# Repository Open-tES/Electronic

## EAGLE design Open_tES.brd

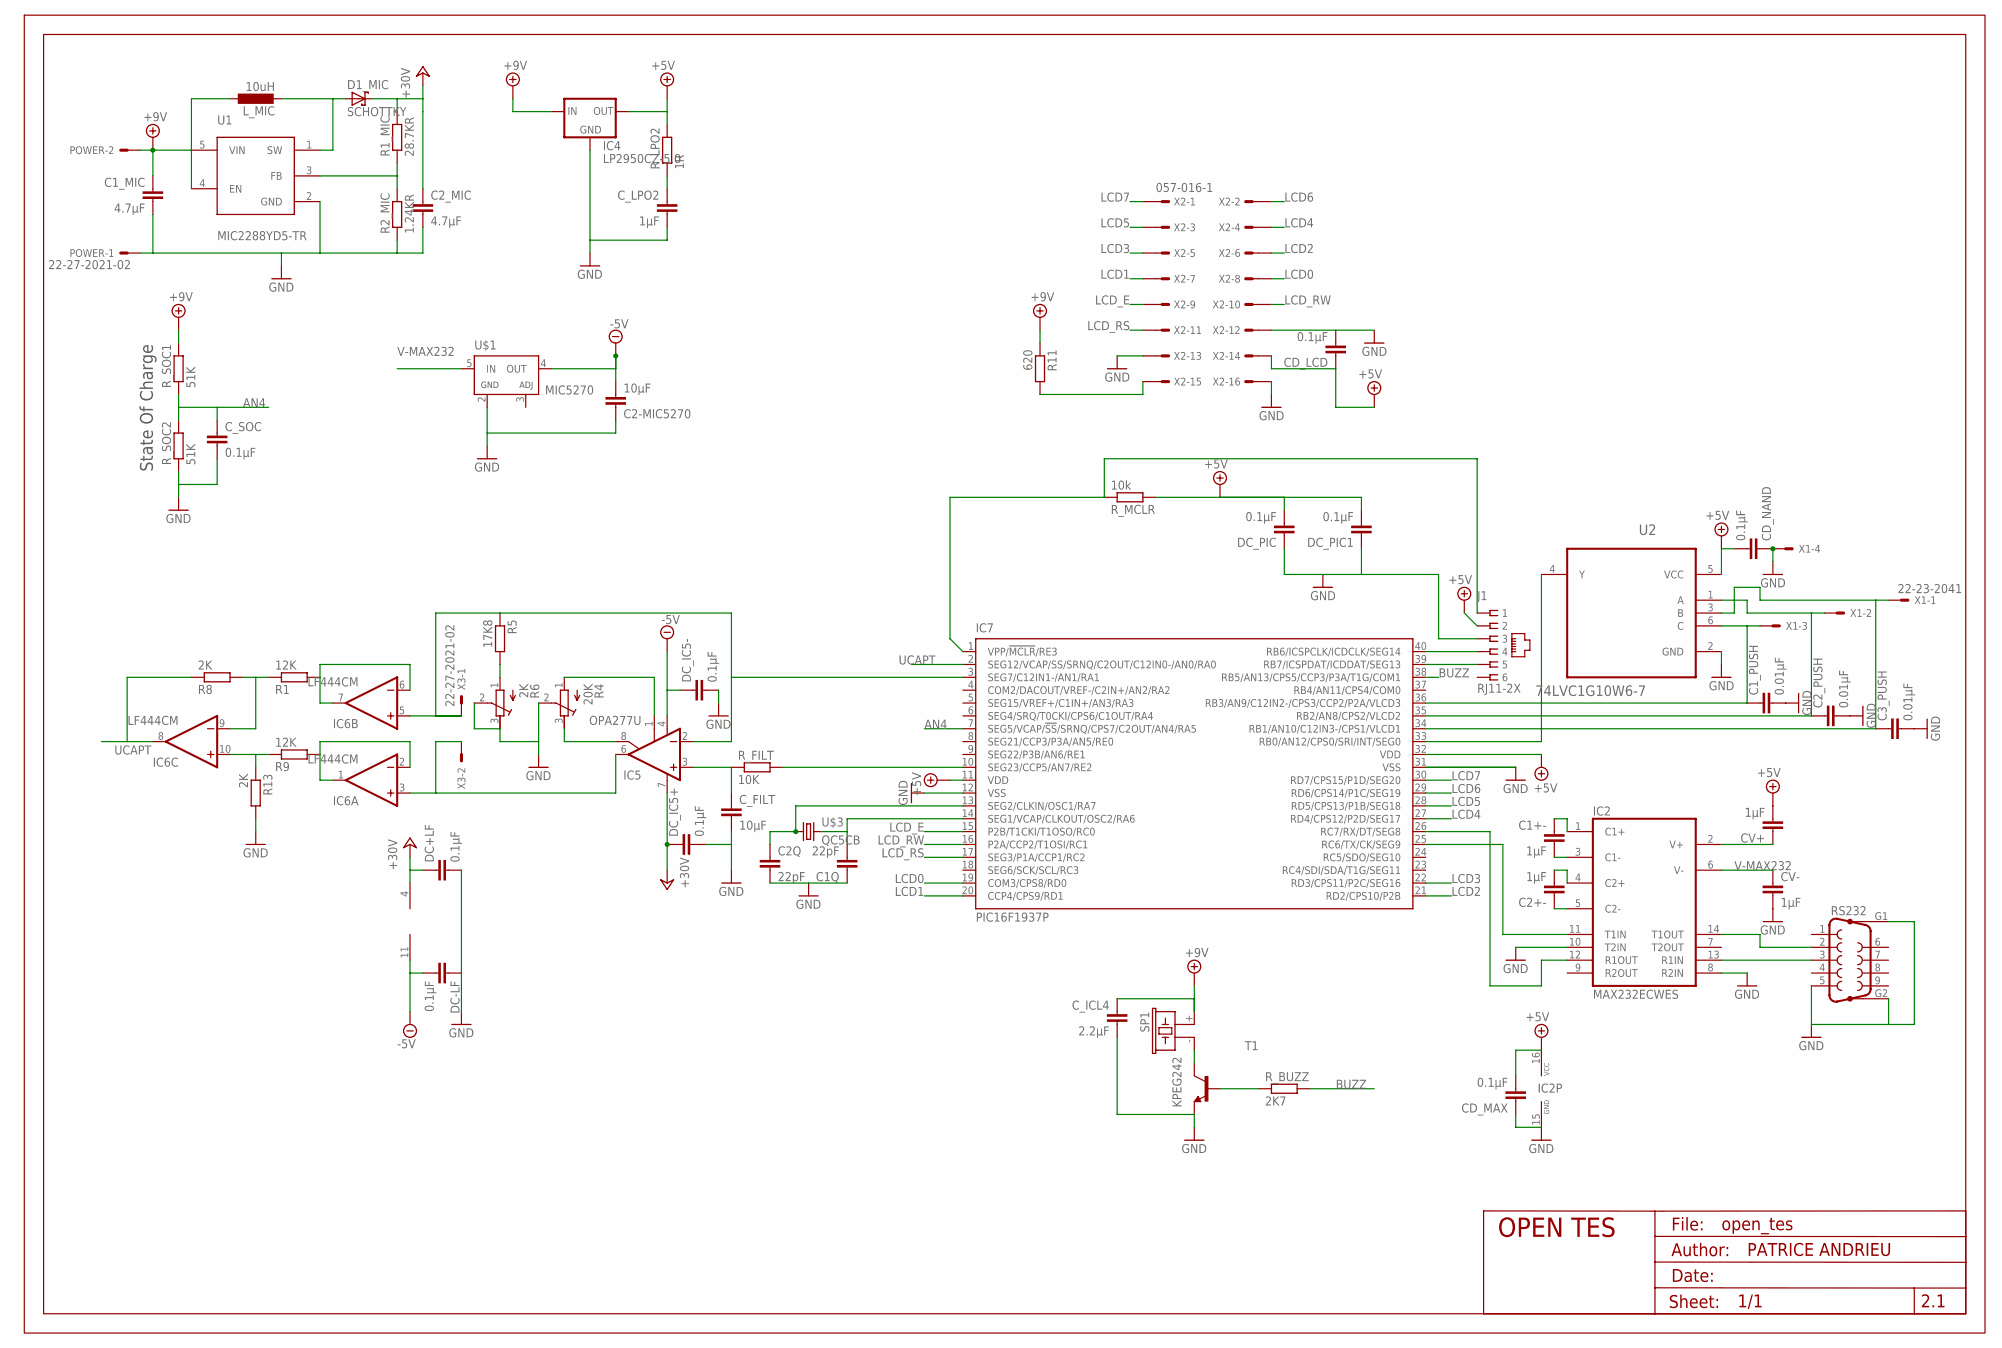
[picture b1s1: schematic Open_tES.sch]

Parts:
C1+-, C2+-: 1µF; C0805
C1Q, C2Q: 22pF; C0805
C1_MIC, C2_MIC: 4.7µF; C0805
C1_PUSH, C2_PUSH, C3_PUSH: 0.01µF; C0805
C2-MIC5270: 10µF; C0805
CD_LCD: 0.1µF; C0805
CD_MAX: 0.1µF; C0805
CD_NAND: 0.1µF; C0805
CV+: 1µF; C0805
CV-: 1µF; C0805
C_FILT: 10µF; C0805
C_ICL4: 2.2µF; C0805K
C_LPO2: 1µF; C0805
C_SOC: 0.1µF; C0805
D1_MIC: SCHOTTKY; SOD80
DC+LF: 0.1µF; C0805
DC-LF: 0.1µF; C0805
DC_IC5+, DC_IC5-: 0.1µF; C0805
DC_PIC, DC_PIC1: 0.1µF; C0805
IC2: MAX232ECWES; SO16
IC4: LP2950CZ-5.0; TO92
IC5: OPA277U; SO08
IC6: LF444CM; SO14
IC7: PIC16F1937P; DIL40
J1: RJ11-2X; RJ11-NO_SHIELD
L_MIC: 10uH; L2012C
POWER: 22-27-2021-02; 6410-02
R1, R9: 12K; R0805
R1_MIC: 28.7KR; R0805
R2_MIC: 1.24KR; R0805
R4: 20K; RTRIM3214W
R5: 17K8; M0805
R6: 2K; RTRIM3214W
R8, R13: 2K; R0805
R11: 620; 0204/7
RS232: F09HP
R_BUZZ: 2K7; R0805
R_FILT: 10K; R0805
R_LPO2: 1R; R0805
R_MCLR: 10k; 0204/7
R_SOC1, R_SOC2: 51K; R0805
SP1: KPEG242
T1: BFR92-NPN-SOT23-BEC; SOT23-BEC
U1: MIC2288YD5-TR; SOT23-5L
U2: 74LVC1G10W6-7; SOT95P280X135-6N
U$1: MIC5270; SOT23-5L
U$3: QC5CB
U$4: FRAME; OPEN_TE_VERSION
X1: 22-23-2041
X2: 057-016-1
X3: 22-27-2021-02; 6410-02

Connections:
+5V/1: CD_LCD.1, CD_MAX.2, CD_NAND.2, CV+.2, DC_PIC.2, DC_PIC1.2, IC2.16 (VCC), IC4.1 (OUT), IC7.11 (VDD), IC7.32 (VDD), J1.2, R_LPO2.2, R_MCLR.2, U2.5 (VCC), X2.14
+9V: C1_MIC.1, C_ICL4.1, IC4.3 (IN), L_MIC.1, POWER.2, R11.1, R_SOC1.2, SP1.+ (1), U1.4 (EN), U1.5 (VIN)
+30V: C2_MIC.1, D1_MIC.C, DC+LF.1, DC_IC5+.1, IC5.7 (V+), IC6.4 (V+), R1_MIC.2
-5V: C2-MIC5270.2, DC-LF.2, DC_IC5-.1, IC5.4 (V-), IC6.11 (V-), U$1.4 (OUT)
AN4: C_SOC.1, IC7.7 (SEG5/VCAP/!SS!/SRNQ/CPS7/C2OUT/AN4/RA5), R_SOC1.1, R_SOC2.2
BUZZ: IC7.38 (RB5/AN13/CPS5/CCP3/P3A/T1G/COM1), R_BUZZ.2
GND: C1Q.1, C1_MIC.2, C1_PUSH.2, C2-MIC5270.1, C2Q.2, C2_MIC.2, C2_PUSH.2, C3_PUSH.2, CD_LCD.2, CD_MAX.1, CD_NAND.1, CV-.2, C_FILT.2, C_ICL4.2, C_LPO2.2, C_SOC.2, DC+LF.2, DC-LF.1, DC_IC5+.2, DC_IC5-.2, DC_PIC.1, DC_PIC1.1, IC2.8 (R2IN), IC2.10 (T2IN), IC2.15 (GND), IC4.2 (GND), IC7.12 (VSS), IC7.31 (VSS), J1.3, POWER.1, R2_MIC.1, R4.2 (S), R6.2 (S), R6.3 (E), R13.2, RS232.5, RS232.G1, RS232.G2, R_SOC2.1, T1.E, U1.2 (GND), U2.2 (GND), U$1.2 (GND), X1.4, X2.12, X2.13, X2.16
ICAPT: IC5.2 (-IN), IC6.5 (+IN), IC7.3 (SEG7/C12IN1-/AN1/RA1), R5.1, X3.1
LCD0: IC7.19 (COM3/CPS8/RD0), X2.8
LCD1: IC7.20 (CCP4/CPS9/RD1), X2.7
LCD2: IC7.21 (RD2/CPS10/P2B), X2.6
LCD3: IC7.22 (RD3/CPS11/P2C/SEG16), X2.5
LCD4: IC7.27 (RD4/CPS12/P2D/SEG17), X2.4
LCD5: IC7.28 (RD5/CPS13/P1B/SEG18), X2.3
LCD6: IC7.29 (RD6/CPS14/P1C/SEG19), X2.2
LCD7: IC7.30 (RD7/CPS15/P1D/SEG20), X2.1
LCD_E: IC7.15 (P2B/T1CKI/T1OSO/RC0), X2.9
LCD_RS: IC7.17 (SEG3/P1A/CCP1/RC2), X2.11
LCD_RW: IC7.16 (P2A/CCP2/T1OSI/RC1), X2.10
MCLR: IC7.1 (VPP/!MCLR!/RE3), J1.1, R_MCLR.1
unnamed: SP1.- (2), T1.C
unnamed: IC6.6 (-IN), IC6.7 (OUT), R1.2
unnamed: C1+-.1, IC2.1 (C1+)
unnamed: R5.2, R6.1 (A)
unnamed: C2+-.2, IC2.4 (C2+)
unnamed: C1Q.2, IC7.14 (SEG1/VCAP/CLKOUT/OSC2/RA6), U$3.2
unnamed: IC2.14 (T1OUT), RS232.2
unnamed: IC2.13 (R1IN), RS232.3
unnamed: C3_PUSH.1, IC7.34 (RB1/AN10/C12IN3-/CPS1/VLCD1), U2.3 (B), X1.1
unnamed: R1_MIC.1, R2_MIC.2, U1.3 (FB)
unnamed: IC2.11 (T1IN), IC7.25 (RC6/TX/CK/SEG9)
unnamed: R_BUZZ.1, T1.B
unnamed: IC6.10 (+IN), R9.1, R13.1
unnamed: IC6.9 (-IN), R1.1, R8.2
unnamed: IC2.12 (R1OUT), IC7.26 (RC7/RX/DT/SEG8)
unnamed: IC5.8 (CMP2), R4.3 (E)
unnamed: IC6.1 (OUT), IC6.2 (-IN), R9.2
unnamed: C1_PUSH.1, IC7.36 (RB3/AN9/C12IN2-/CPS3/CCP2/P2A/VLCD3), U2.6 (C), X1.3
unnamed: C_FILT.1, IC5.3 (+IN), R_FILT.1
unnamed: C2Q.1, IC7.13 (SEG2/CLKIN/OSC1/RA7), U$3.1
unnamed: C_LPO2.1, R_LPO2.1
unnamed: C1+-.2, IC2.3 (C1-)
unnamed: C2_PUSH.1, IC7.35 (RB2/AN8/CPS2/VLCD2), U2.1 (A), X1.2
unnamed: IC7.33 (RB0/AN12/CPS0/SRI/INT/SEG0), U2.4 (Y)
unnamed: IC5.1 (CMP1), R4.1 (A)
unnamed: IC5.6 (OUT), IC6.3 (+IN), X3.2
unnamed: C2+-.1, IC2.5 (C2-)
unnamed: CV+.1, IC2.2 (V+)
unnamed: R11.2, X2.15
unnamed: D1_MIC.A, L_MIC.2, U1.1 (SW)
PGC: IC7.39 (RB7/ICSPDAT/ICDDAT/SEG13), J1.5
PGD: IC7.40 (RB6/ICSPCLK/ICDCLK/SEG14), J1.4
PWM: IC7.10 (SEG23/CCP5/AN7/RE2), R_FILT.2
UCAPT: IC6.8 (OUT), IC7.2 (SEG12/VCAP/SS/SRNQ/C2OUT/C12IN0-/AN0/RA0), R8.1
V-MAX232: CV-.1, IC2.6 (V-), U$1.5 (IN)

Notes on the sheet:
State Of Charge

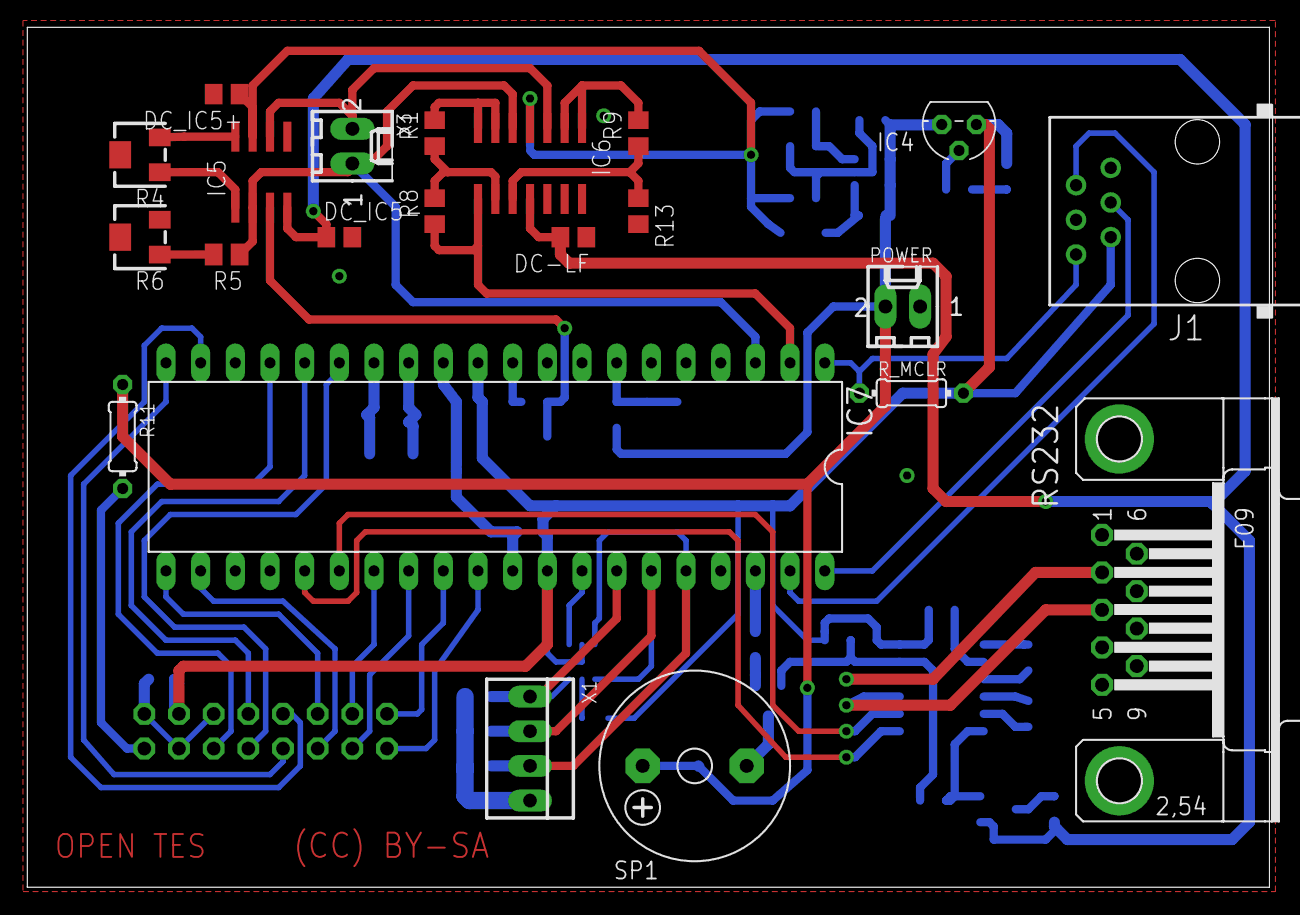
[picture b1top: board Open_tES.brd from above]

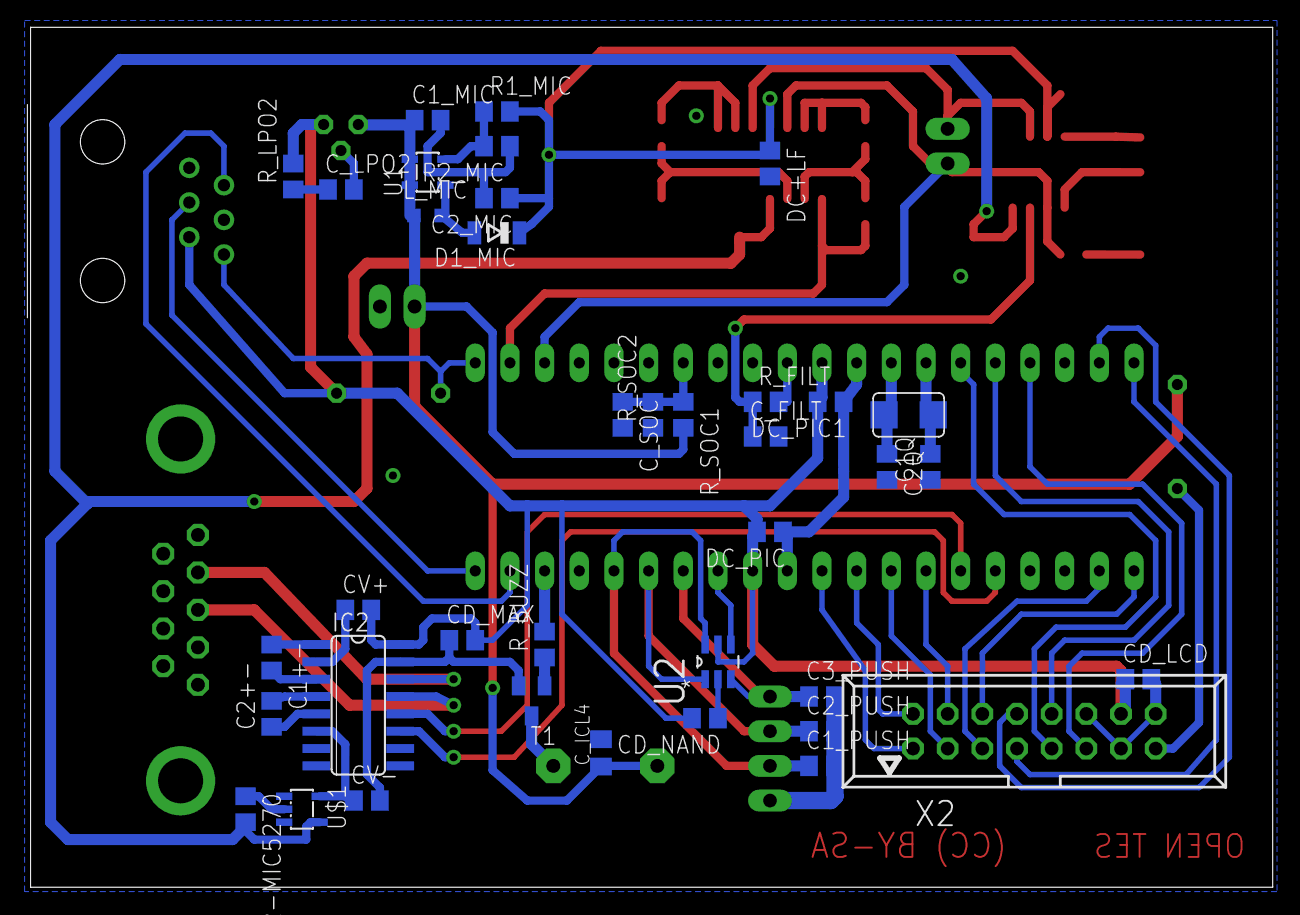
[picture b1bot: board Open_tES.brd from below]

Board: 2 copper layers, 91.2 x 63.0 mm, 61 parts (38 on the bottom side), 55 nets.

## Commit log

2016-01-20 adding of gitignore file
2016-01-20 Adding of files project -first commit-
2016-01-20 removing supply 28+(not used)
2016-01-21 replace TSR on the shematic by MIC2288 boost DC-DC
2016-01-21 backlight resistor for 9V supply
2016-01-22 Open_tES.lbr update
2016-01-22 use of MAX232 for negative voltage with MIC5270 for regulation (-5V)
2016-01-22 Changing of RJ connector with 90deg connector to ease PIC programming. Need a new hole in back end plate
2016-01-22 1)replace 4023 triple 3-input NAND with 74LVC1G10W6-7 simple 3-input NAND 2) solve consistent problem between sch and brd
2016-01-22 update version on the schem and board -2.0-
2016-01-25 fixing of connecting error +9V and +30V. MIC2288 and LP2950 was concerned. Correction of capacitor for LPO.
2016-01-25 Removing input capacitor for LPO: C1_MIC already present.
2016-02-03 library update: QC5CB tPlace, MIC5270 OC_FARNELL, SCHOTTKY
2016-02-03 Adding of state of charge module connecting to AN4: firmware updating is necessary. End of routing
2016-02-08 Changing of C_FILT value 22->10uc to simplify the circuit. The same capacitor is already used on the board : C2-MIC5270
2016-02-08 replace package of R1 R8 R9 R13 MELF->0805 to reduce the cost. Update version 2.0->2.1 in files
2016-03-02 Fixing of several mistakes concerning component references. Changing of package for the trimmers R4 R6.
